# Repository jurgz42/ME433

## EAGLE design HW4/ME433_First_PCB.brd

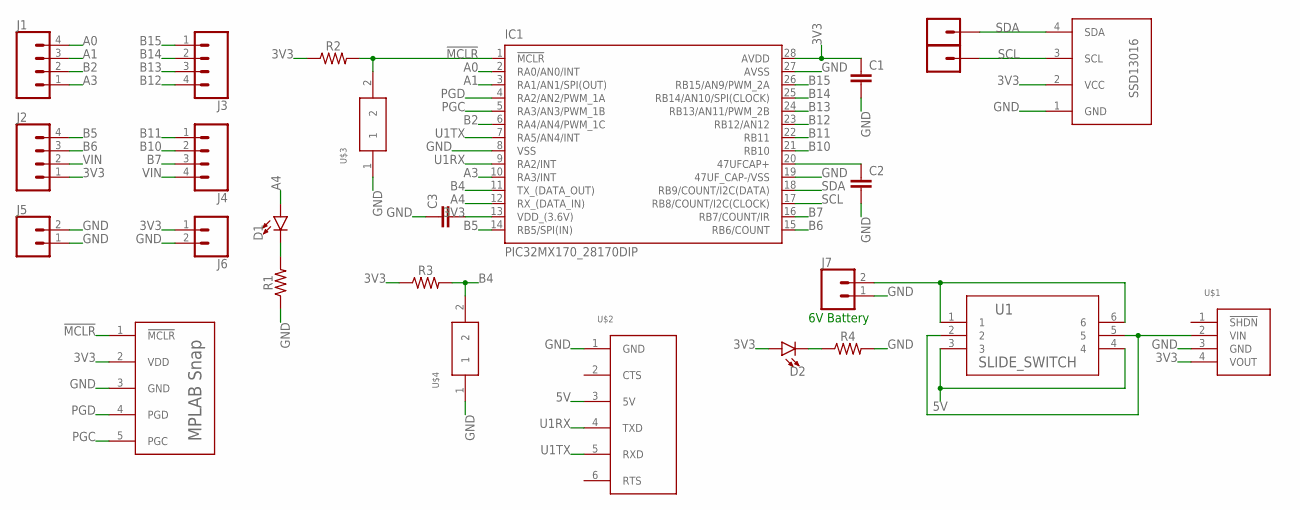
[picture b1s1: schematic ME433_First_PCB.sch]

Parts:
C1, C2, C3: C-EU025-025X050; C025-025X050
D1, D2: LED3MM; LED_3MM
IC1: PIC32MX170_28170DIP; DIL28-3
J1, J2, J3, J4: CONN_04; 1X04
J5, J6, J7: CONN_02; 1X02
J8, J9: CONN_01; 1X01
OLED: OLED_SCREEN
R1, R2, R3, R4: 1M; AXIAL-0.3
U1: SLIDE_SWITCH; SWITCH_011CQN
U$1: POLOLU_3V3_VREG
U$2: ADAFRUIT_CP2104
U$3, U$4: BUTTON
U$5: MPLAB_SNAP

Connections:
3V3: C1.1, C3.2, D2.A, IC1.13 (VDD_(3.6V)), IC1.28 (AVDD), J2.1, J6.1, OLED.2 (VCC), R2.P$1 (1), R3.P$1 (1), U$1.4 (VOUT), U$5.2 (VDD)
5V: U1.3, U1.4, U$2.3 (5V)
!MCLR: IC1.1 (!MCLR!), R2.P$2 (2), U$3.2, U$5.1 (!MCLR)
A0: IC1.2 (RA0/AN0/INT), J1.4
A1: IC1.3 (RA1/AN1/SPI(OUT)), J1.3
A3: IC1.10 (RA3/INT), J1.1
A4: D1.A, IC1.12 (RX_(DATA_IN))
B2: IC1.6 (RA4/AN4/PWM_1C), J1.2
B4: IC1.11 (TX_(DATA_OUT)), R3.P$2 (2), U$4.2
B5: IC1.14 (RB5/SPI(IN)), J2.4
B6: IC1.15 (RB6/COUNT), J2.3
B7: IC1.16 (RB7/COUNT/IR), J4.3
B10: IC1.21 (RB10), J4.2
B11: IC1.22 (RB11), J4.1
B12: IC1.23 (RB12/AN12), J3.4
B13: IC1.24 (RB13/AN11/PWM_2B), J3.3
B14: IC1.25 (RB14/AN10/SPI(CLOCK)), J3.2
B15: IC1.26 (RB15/AN9/PWM_2A), J3.1
GND: C1.2, C2.2, C3.1, IC1.8 (VSS), IC1.19 (47UF_CAP-/VSS), IC1.27 (AVSS), J5.1, J5.2, J6.2, J7.1, OLED.1 (GND), R1.P$1 (1), R4.P$2 (2), U$1.3 (GND), U$2.1 (GND), U$3.1, U$4.1, U$5.3 (GND)
unnamed: C2.1, IC1.20 (47UFCAP+)
unnamed: D1.K (C), R1.P$2 (2)
unnamed: D2.K (C), R4.P$1 (1)
unnamed: J7.2, U1.1, U1.6
PGC: IC1.5 (RA3/AN3/PWM_1B), U$5.5 (PGC)
PGD: IC1.4 (RA2/AN2/PWM_1A), U$5.4 (PGD)
SCL: IC1.17 (RB8/COUNT/I2C(CLOCK)), J9.1, OLED.3 (SCL)
SDA: IC1.18 (RB9/COUNT/I2C(DATA)), J8.1, OLED.4 (SDA)
U1RX: IC1.9 (RA2/INT), U$2.4 (TXD)
U1TX: IC1.7 (RA5/AN4/INT), U$2.5 (RXD)
VIN: J2.2, J4.4, U1.2, U1.5, U$1.2 (VIN)

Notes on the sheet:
6V Battery

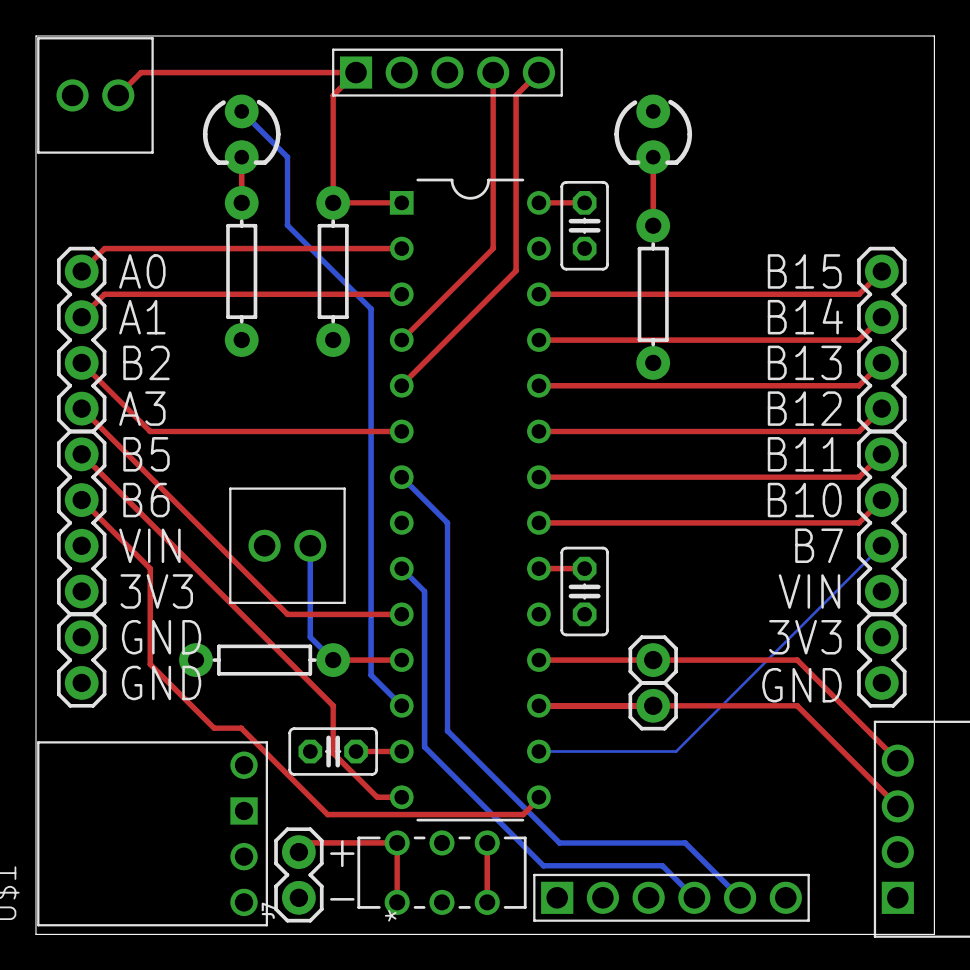
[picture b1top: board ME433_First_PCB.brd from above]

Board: 4 copper layers, 49.9 x 49.9 mm, 26 parts (0 on the bottom side), 30 nets.

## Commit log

2022-04-05 HW2 finished
2022-04-19 HW5 image
2022-04-28 HW7 - IMU
2022-04-29 OLED Display
2022-05-10 NeoPixels
2022-05-12 Intro to CircuitPy
2022-05-18 Taking a Picture

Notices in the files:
parts and their libraries:
SparkFun-Connectors: Licensing: Creative Commons ShareAlike 4.0 International - https://creativecommons.org/licenses/by-sa/4.0
COPYRIGHT: Copyright (C) 2022 Ultra Librarian. All rights reserved.
